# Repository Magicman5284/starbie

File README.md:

Welcome to my Starbie project!

This is my first project for the hackclub halflife program. 

I chose to do the starby beginner project because I had never designed a circuit board before, and I wanted to start with something easier. 

About halfway through I decided to change the project a bit and add more keys so that it can also act as a macropad. 

I figured that just a virtual pet wouldn't have much use, so I decided to make it so that it also had a use outside of that!

The rocket ship shape and icon were chosen because that's the icon I've used for online profiles for many years now, and I wanted it to have a presence on the board. 

Bom: 
|Item                    |Qty|Supplier  |Cost/item|Total Cost|link                                                                                                                                                                                                                                                                                                                                                                                                                                                                                                                                                                                                                                        |
|------------------------|---|----------|---------|----------|--------------------------------------------------------------------------------------------------------------------------------------------------------------------------------------------------------------------------------------------------------------------------------------------------------------------------------------------------------------------------------------------------------------------------------------------------------------------------------------------------------------------------------------------------------------------------------------------------------------------------------------------|
|PCB                     |1  |JLCPCB    |$11.19   |$11.19    |https://cart.jlcpcb.com/quote                                                                                                                                                                                                                                                                                                                                                                                                                                                                                                                                                                                                               |
|Keyboard switches       |1  |Aliexpress|$3.80    |$3.80     |https://www.aliexpress.us/item/3256809144133324.html?spm=a2g0o.productlist.main.1.231822a6QUJ8NU&algo_pvid=68ff24c1-f75c-4a2d-ae06-b67478f7996d&algo_exp_id=68ff24c1-f75c-4a2d-ae06-b67478f7996d-0&pdp_ext_f=%7B%22order%22%3A%22163%22%2C%22eval%22%3A%221%22%2C%22fromPage%22%3A%22search%22%7D&pdp_npi=6%40dis%21USD%213.80%213.80%21%21%2125.34%2125.34%21%4021030cd817915061702678482e106a%2112000048776240763%21sea%21US%212783459362%21X%211%210%21n_tag%3A-29919%3Bd%3Abaf43391%3Bm03_new_user%3A-29895&curPageLogUid=b3GQDNLvSzGG&utparam-url=scene%3Asearch%7Cquery_from%3A%7Cx_object_id%3A1005009330448076%7C_p_origin_prod%3A  |
|Keycaps                 |1  |Aliexpress|$2.50    |$2.50     |https://www.aliexpress.us/item/3256812392832257.html?spm=a2g0o.productlist.main.9.550e4e9dmWrA8p&algo_pvid=2eca2c9e-c268-4d1d-afa3-f60a7611ed69&algo_exp_id=2eca2c9e-c268-4d1d-afa3-f60a7611ed69-8&pdp_ext_f=%7B%22order%22%3A%22101%22%2C%22eval%22%3A%221%22%2C%22fromPage%22%3A%22search%22%7D&pdp_npi=6%40dis%21USD%212.50%212.50%21%21%2116.68%2116.68%21%402101c4b817915062699036540e0eb1%2112000058776520557%21sea%21US%212783459362%21X%211%210%21n_tag%3A-29919%3Bd%3Abaf43391%3Bm03_new_user%3A-29895&curPageLogUid=PSGgFm78zvfs&utparam-url=scene%3Asearch%7Cquery_from%3A%7Cx_object_id%3A1005012579147009%7C_p_origin_prod%3A  |
|DHT11                   |1  |Aliexpress|$1.89    |$1.89     |https://www.aliexpress.us/item/3256808632582299.html?spm=a2g0o.productlist.main.1.6ce61b79jkeE3E&algo_pvid=98b69c66-6a43-4e4f-80e4-13763e0766e9&algo_exp_id=98b69c66-6a43-4e4f-80e4-13763e0766e9-0&pdp_ext_f=%7B%22order%22%3A%22112%22%2C%22eval%22%3A%221%22%2C%22fromPage%22%3A%22search%22%7D&pdp_npi=6%40dis%21USD%211.89%211.89%21%21%2112.57%2112.57%21%402101e81117915069522787752e13ea%2112000046802736833%21sea%21US%212783459362%21X%211%210%21n_tag%3A-29919%3Bd%3Abaf43391%3Bm03_new_user%3A-29895&curPageLogUid=AI5yCX14P0mZ&utparam-url=scene%3Asearch%7Cquery_from%3A%7Cx_object_id%3A1005008818897051%7C_p_origin_prod%3A  |
|MPU6050                 |1  |aliexpress|$2.10    |$2.10     |https://www.aliexpress.us/item/3256809871479525.html?spm=a2g0o.productlist.main.10.39224922NbFEFY&algo_pvid=188ded79-5577-4a28-a4c5-ad7c7b57545b&algo_exp_id=188ded79-5577-4a28-a4c5-ad7c7b57545b-9&pdp_ext_f=%7B%22order%22%3A%223402%22%2C%22eval%22%3A%221%22%2C%22fromPage%22%3A%22search%22%7D&pdp_npi=6%40dis%21USD%212.10%212.10%21%21%212.10%212.10%21%402101dedf17915070209742571e0f7f%2112000050979433010%21sea%21US%212783459362%21X%211%210%21n_tag%3A-29919%3Bd%3Abaf43391%3Bm03_new_user%3A-29895&curPageLogUid=xWEKQUcyBYax&utparam-url=scene%3Asearch%7Cquery_from%3A%7Cx_object_id%3A1005010057794277%7C_p_origin_prod%3A  |
|OLED screen             |1  |aliexpress|$2.21    |$2.21     |https://www.aliexpress.us/item/3256804169233174.html?spm=a2g0o.productlist.main.2.7ba066ba6Ejke9&algo_pvid=f11b7aef-e40a-4971-8f13-a0a17324e477&algo_exp_id=f11b7aef-e40a-4971-8f13-a0a17324e477-1&pdp_ext_f=%7B%22order%22%3A%224416%22%2C%22eval%22%3A%221%22%2C%22fromPage%22%3A%22search%22%7D&pdp_npi=6%40dis%21USD%212.21%212.21%21%21%2114.76%2114.76%21%402103081117915072484156336e0f79%2112000048256636851%21sea%21US%212783459362%21X%211%210%21n_tag%3A-29919%3Bd%3Abaf43391%3Bm03_new_user%3A-29895&curPageLogUid=xP2vkBBggNW6&utparam-url=scene%3Asearch%7Cquery_from%3A%7Cx_object_id%3A1005004355547926%7C_p_origin_prod%3A |
|XIAO ESP32-C3           |1  |Aliexpress|$8.83    |$8.83     |https://www.aliexpress.us/item/3256809899117724.html?spm=a2g0o.productlist.main.15.3dd943b7HAQiFh&algo_pvid=f4215073-c1da-4504-b8d0-5101ada3dc61&algo_exp_id=f4215073-c1da-4504-b8d0-5101ada3dc61-12&pdp_ext_f=%7B%22order%22%3A%22148%22%2C%22eval%22%3A%221%22%2C%22fromPage%22%3A%22search%22%7D&pdp_npi=6%40dis%21USD%218.83%218.83%21%21%2158.86%2158.86%21%402101dedf17915073566191411e0f3c%2112000056372508462%21sea%21US%212783459362%21X%211%210%21n_tag%3A-29919%3Bd%3Abaf43391%3Bm03_new_user%3A-29895&curPageLogUid=FYSMpOisDByE&utparam-url=scene%3Asearch%7Cquery_from%3A%7Cx_object_id%3A1005010085432476%7C_p_origin_prod%3A|
|Estimated total shipping|1  |          |         |$0.00     |                                                                                                                                                                                                                                                                                                                                                                                                                                                                                                                                                                                                                                            |

About: 

Starbie is a virtual pet powered by a Seeed XIAO ESP32-C3, with an OLED display, motion sensing, and temperature/humidity readings. It also works as a Bluetooth macropad.

Features

Virtual pet with Joy, Energy, and Fullness stats

Motion-based interactions and pet activities

Bluetooth shortcuts for Copy, Paste, Cut, Undo, and Screenshot

Switch between pet and macropad modes using D2

Hardware: XIAO ESP32-C3, OLED, MPU6050, DHT11, and six buttons.

Libraries: Adafruit SSD1306, Adafruit GFX, MPU6050, DHT, and a compatible BLE Keyboard library.

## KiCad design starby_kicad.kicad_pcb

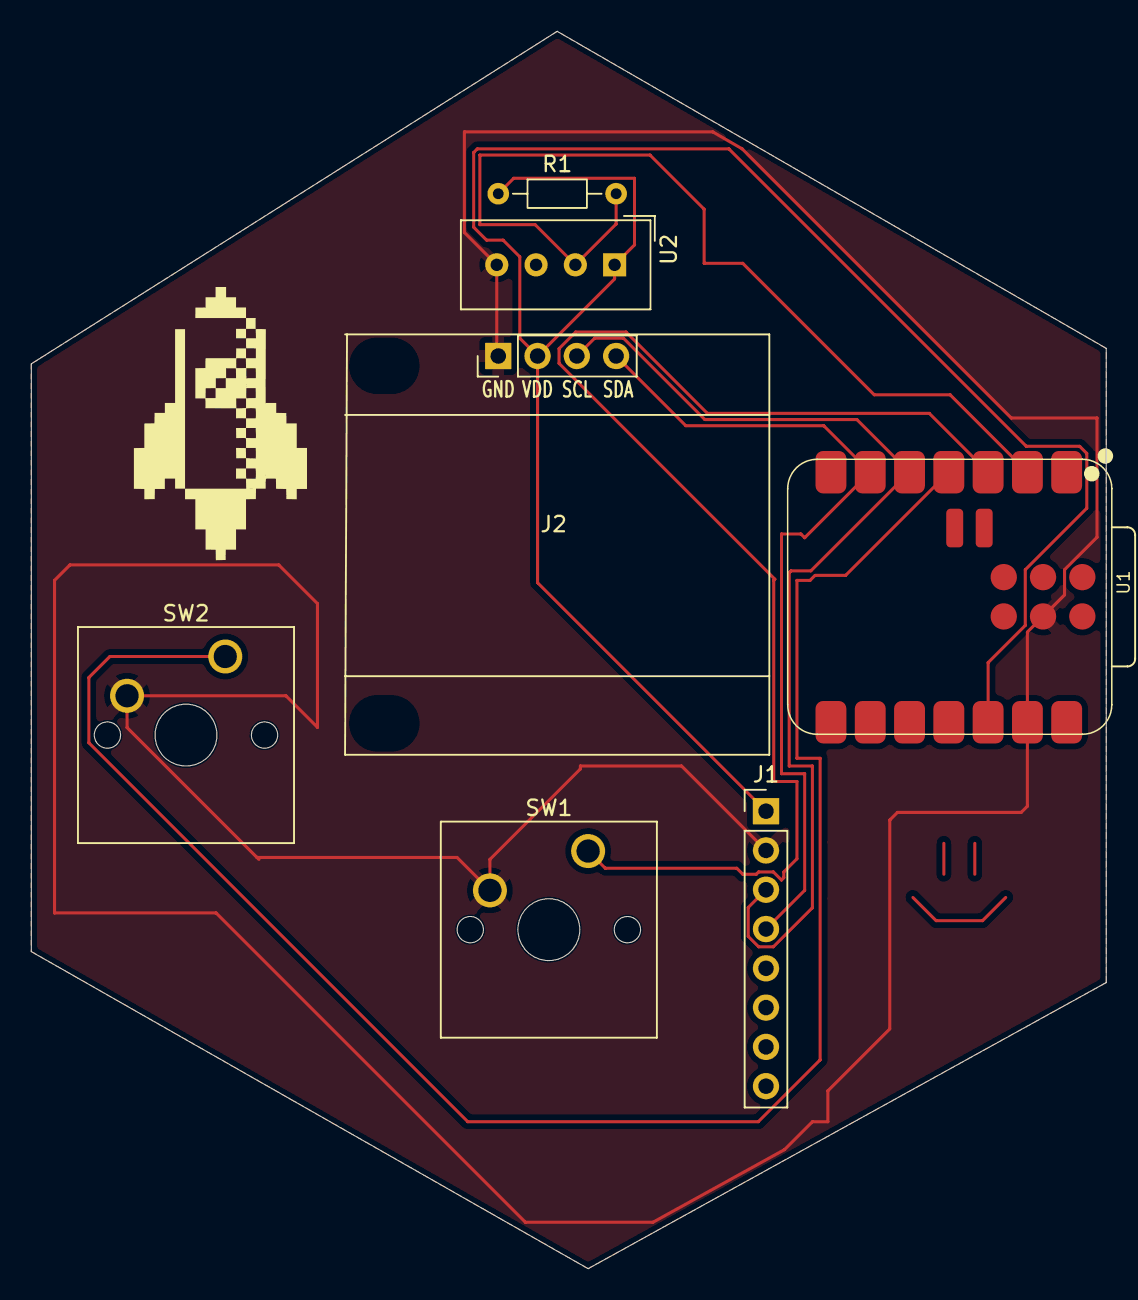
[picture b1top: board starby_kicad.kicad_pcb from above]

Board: 2 copper layers, 69.5 x 80.0 mm, 7 parts (0 on the bottom side), 7 nets.

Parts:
J1: Conn_01x08_Pin; PinHeader_1x08_P2.54mm_Vertical
J2: Conn_01x04_Pin; Display_128x64_096_I2C
R1: 10k; R_Axial_DIN0204_L3.6mm_D1.6mm_P7.62mm_Horizontal
SW1, SW2: SW_Push; SW_Cherry_MX_1.00u_PCB
U1: XIAO-ESP32-C3-SMD
U2: DHT11; Aosong_DHT11_5.5x12.0_P2.54mm

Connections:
+3.3V: J1.1, J2.2, R1.1, U1.12 (3V3_OUT), U2.1 (VDD)
/DHT11 DATA: R1.2, U1.2 (D1), U2.2 (DATA)
/GPIO2: SW1.1, U1.3 (D2)
/GPIO3: SW2.1, U1.4 (D3)
/SCL: J1.3, J2.3, U1.5 (D4)
/SDA: J1.4, J2.4, U1.6 (D5)
GND: J1.2, J2.1, SW1.2, SW2.2, U1.13 (GND), U1.18 (GND), U2.4 (GND)

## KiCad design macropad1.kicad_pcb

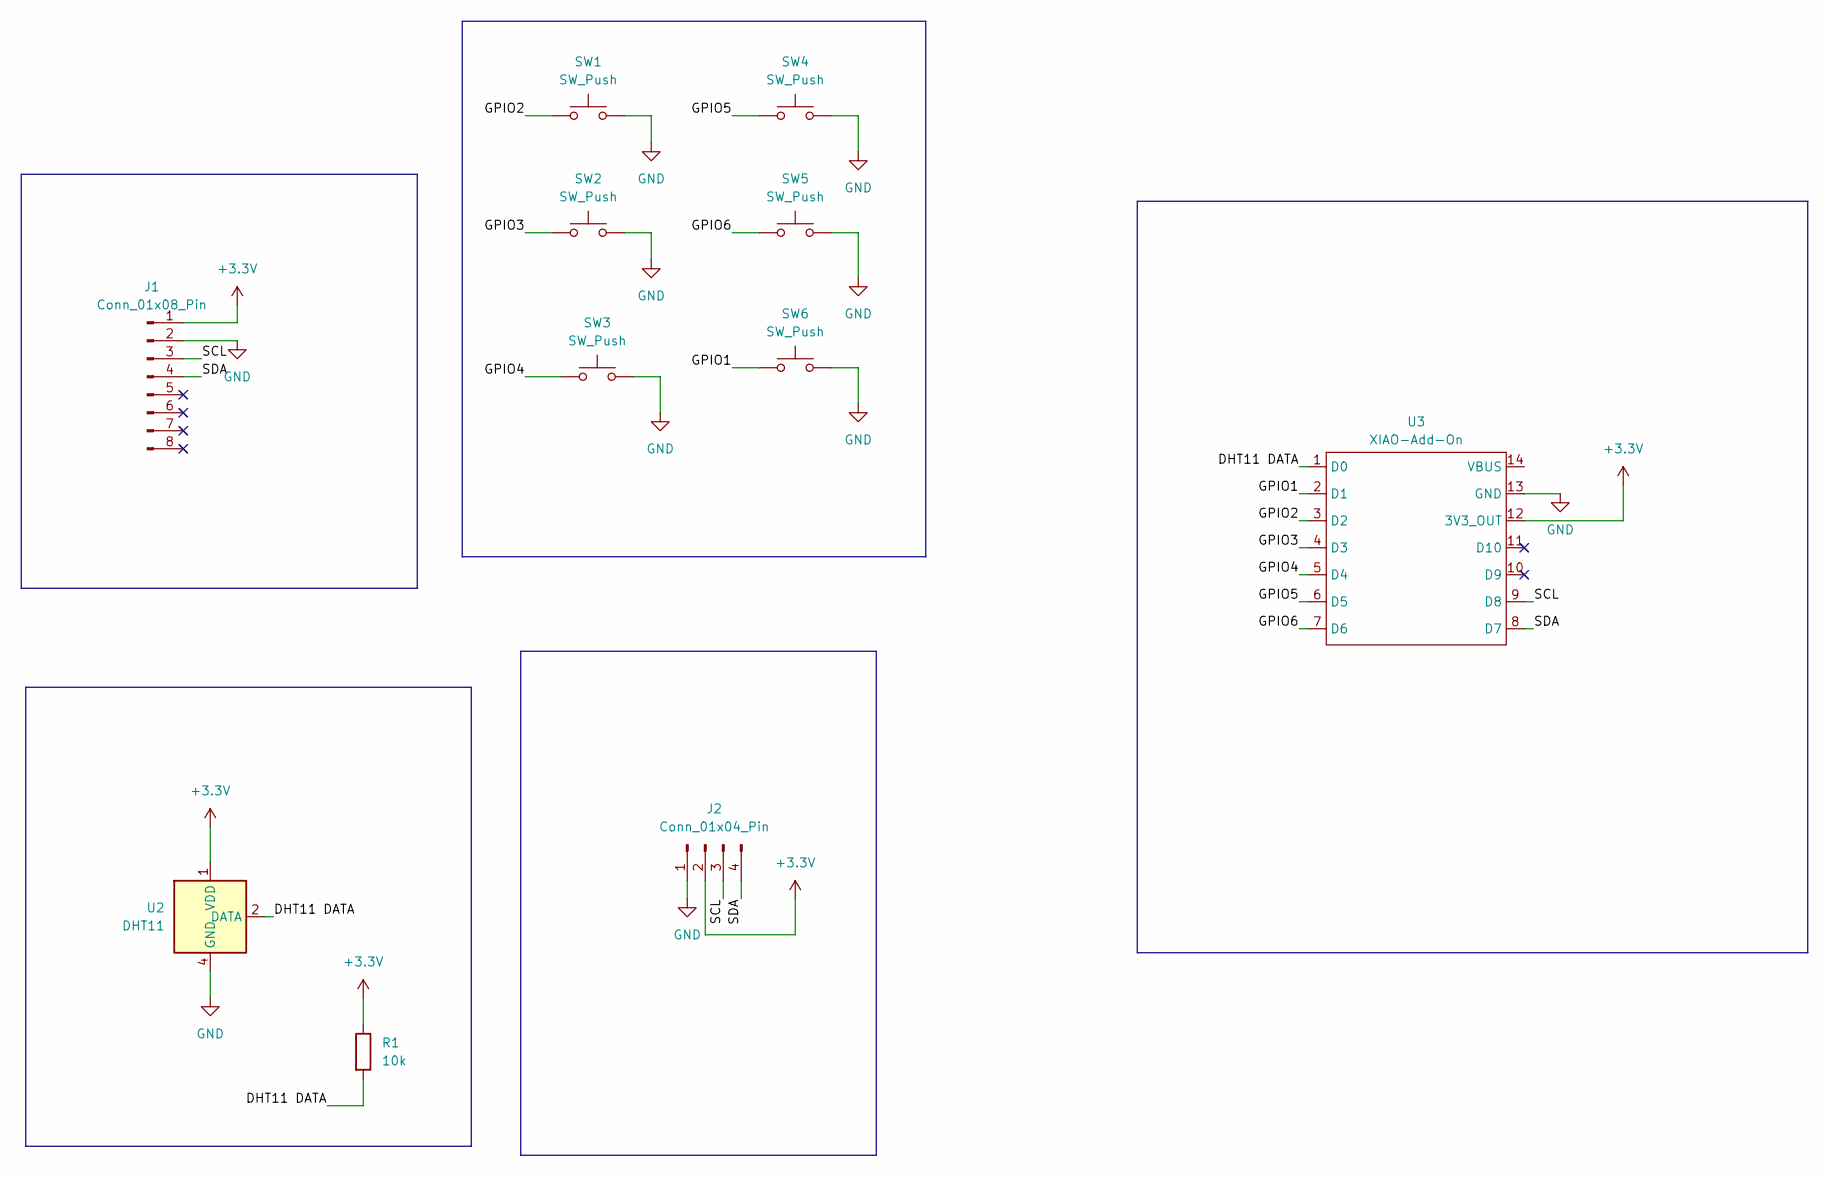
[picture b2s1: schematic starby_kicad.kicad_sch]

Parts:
J1: Conn_01x08_Pin; PinHeader_1x08_P2.54mm_Vertical
J2: Conn_01x04_Pin; Display_128x64_096_I2C
R1: 10k; R_Axial_DIN0204_L3.6mm_D1.6mm_P7.62mm_Horizontal
SW1, SW2, SW3, SW4, SW5, SW6: SW_Push; SW_Cherry_MX_1.00u_PCB
U2: DHT11; Aosong_DHT11_5.5x12.0_P2.54mm
U3: XIAO-Add-On; XIAO-ESP32-C3-DIP

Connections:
+3.3V: J1.1, J2.2, R1.1, U2.1 (VDD), U3.12 (3V3_OUT)
/DHT11 DATA: R1.2, U2.2 (DATA), U3.1 (D0)
/GPIO1: SW6.1, U3.2 (D1)
/GPIO2: SW1.1, U3.3 (D2)
/GPIO3: SW2.1, U3.4 (D3)
/GPIO4: SW3.1, U3.5 (D4)
/GPIO5: SW4.1, U3.6 (D5)
/GPIO6: SW5.1, U3.7 (D6)
/SCL: J1.3, J2.3, U3.9 (D8)
/SDA: J1.4, J2.4, U3.8 (D7)
GND: J1.2, J2.1, SW1.2, SW2.2, SW3.2, SW4.2, SW5.2, SW6.2, U2.4 (GND), U3.13 (GND)

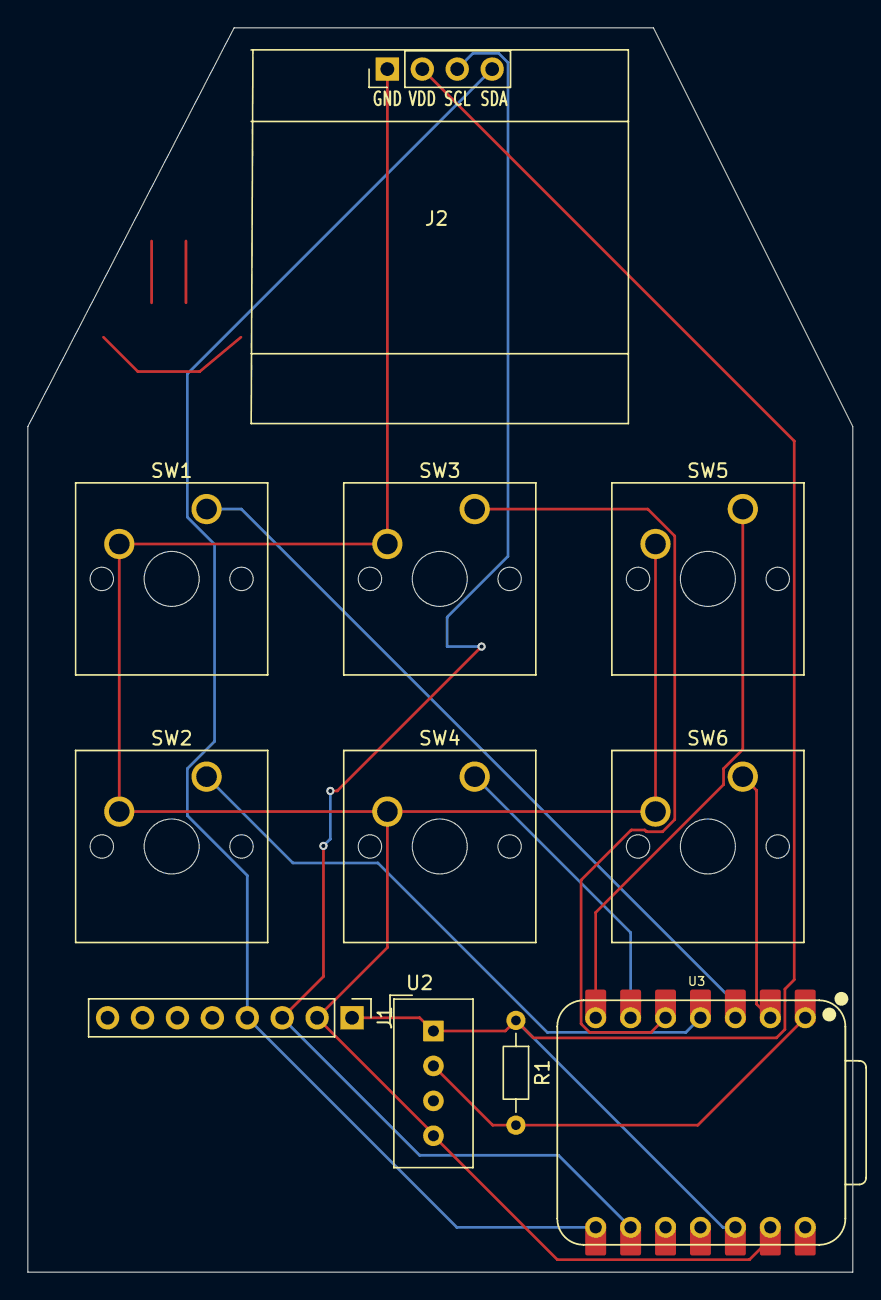
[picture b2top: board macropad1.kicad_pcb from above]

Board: 2 copper layers, 60.0 x 90.5 mm, 11 parts (0 on the bottom side), 11 nets.
